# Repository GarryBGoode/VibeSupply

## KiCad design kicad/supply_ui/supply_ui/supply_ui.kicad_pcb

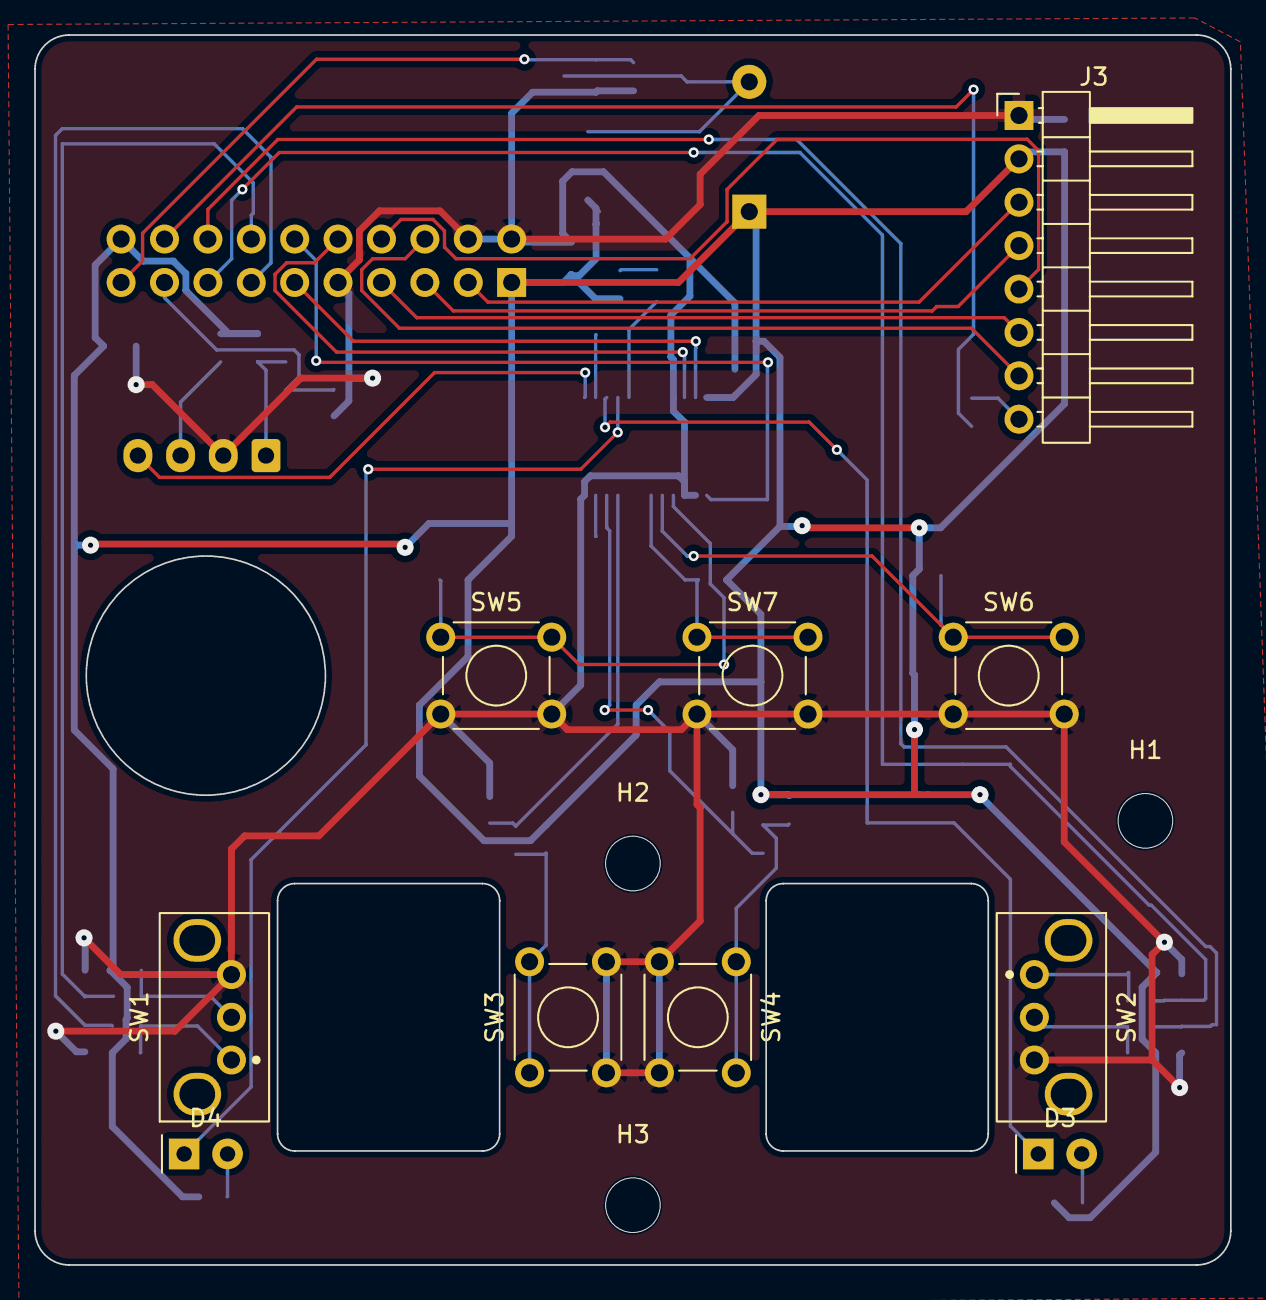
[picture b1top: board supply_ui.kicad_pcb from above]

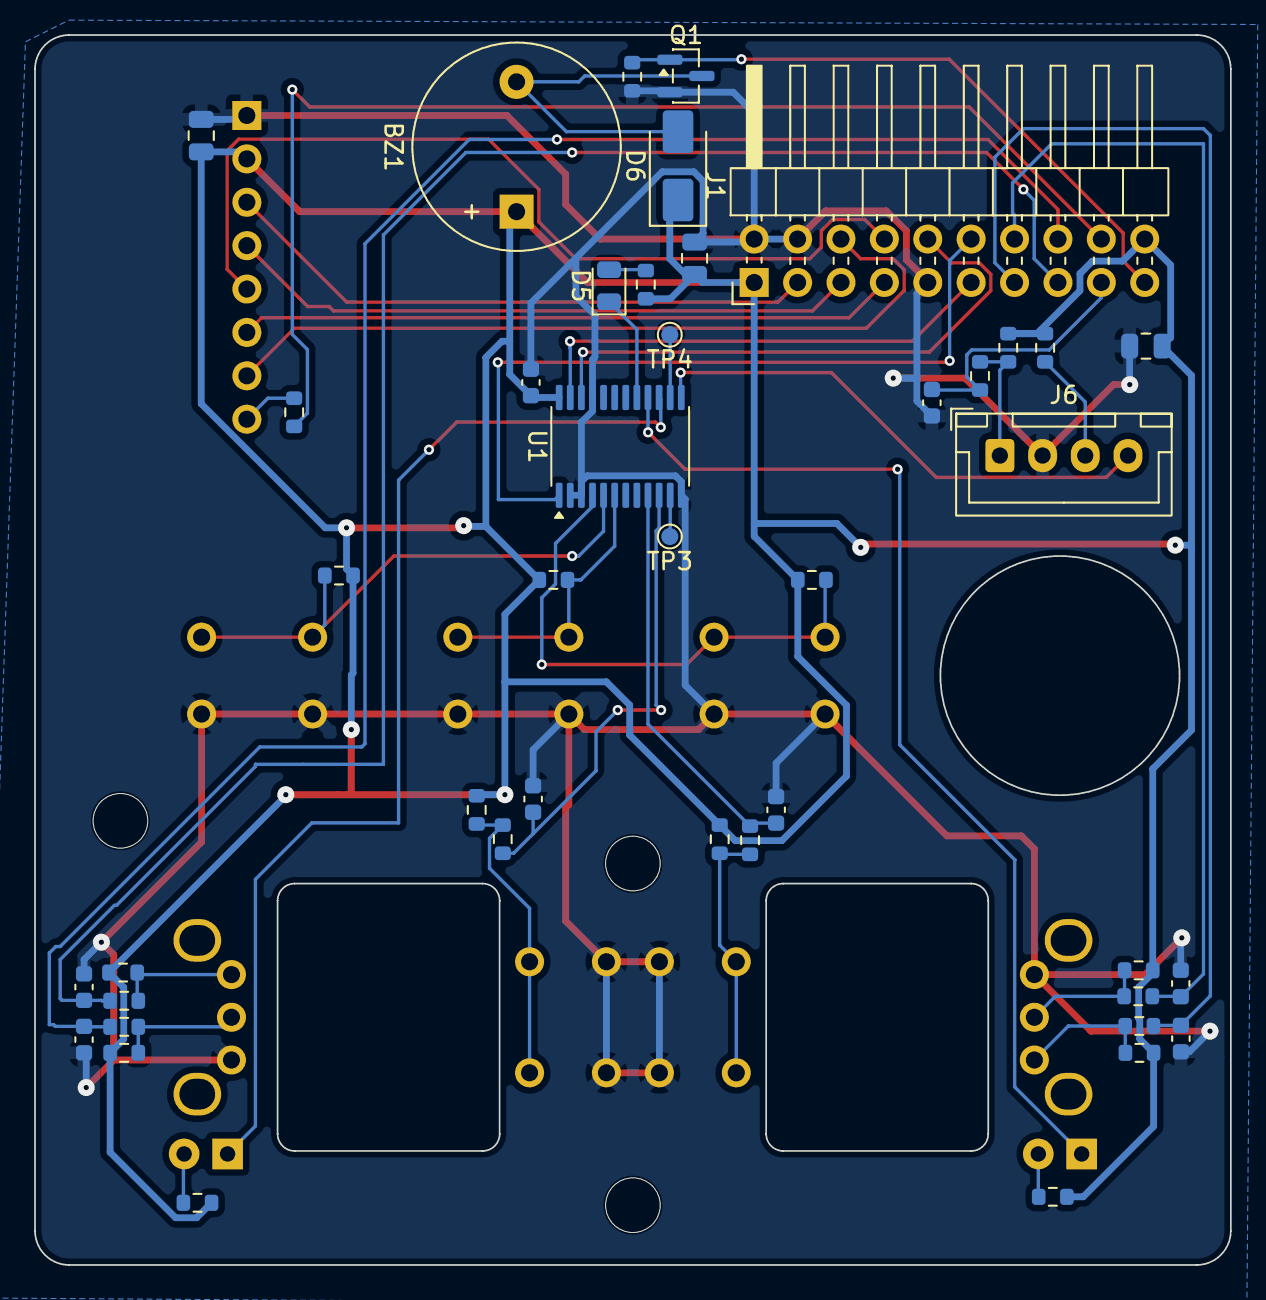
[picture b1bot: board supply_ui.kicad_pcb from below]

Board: 2 copper layers, 70.0 x 72.0 mm, 56 parts (43 on the bottom side), 41 nets.

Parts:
BZ1: magnetic 3V; Buzzer_12x9.5RM7.6
C1, C12: 10u; C_0805_2012Metric
C2: 100n; C_0805_2012Metric
C3, C4, C5, C6, C7, C8, C10: 10n; C_0603_1608Metric
C9: 100n; C_0603_1608Metric
D3: red 3mm diffused CC; LED_D3.0mm_Standoff
D4: green 3mm diffused CV; LED_D3.0mm_Standoff
D5: yellow; LED_0805_2012Metric
D6: SS14; D_SMA
H1, H2, H3: M3; MountingHole_3.2mm_M3
J1: to supply_control; PinHeader_2x10_P2.54mm_Horizontal
J3: IPS 1.9in ST7789 SPI (wired); PinHeader_1x08_P2.54mm_Horizontal
J6: OUTPUT panel button; JST_XH_B4B-XH-A_1x04_P2.50mm_Vertical
Q1: 2N7002; SOT-23
R1, R3, R5, R7, R9, R11, R15, R16, R17, R23: 10k; R_0603_1608Metric
R2, R4, R6, R8, R10, R12, R24: 1k; R_0603_1608Metric
R18, R19, R20: 330; R_0603_1608Metric
R27, R29: 100; R_0603_1608Metric
R28: 100k; R_0603_1608Metric
SW1, SW2: EC10E1220505; RotaryEncoder_Alps_EC10E_Horizontal
SW3: V WHEEL PUSH; SW_TH_Tactile_Omron_B3F-102x
SW4: I WHEEL PUSH; SW_TH_Tactile_Omron_B3F-102x
SW5: LEFT; SW_TH_Tactile_Omron_B3F-102x
SW6: RIGHT; SW_TH_Tactile_Omron_B3F-102x
SW7: ENTER; SW_TH_Tactile_Omron_B3F-102x
TP3, TP4: TestPoint; TestPoint_Pad_D1.0mm
U1: TCA9535PWR; TSSOP-24_4.4x7.8mm_P0.65mm

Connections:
+3V3: BZ1.1, C1.1, C2.1, C9.1, C12.1, D6.1, J1.1, J1.20, J3.2, R1.1, R3.1, R5.1, R7.1, R9.1, R11.1, R15.1, R16.1, R17.1, R18.1, R19.1, R20.1, R23.1, R27.1, U1.24
BTN_ENTER: R17.2, SW7.1, U1.6
BTN_LEFT: R15.2, SW5.1, U1.4
BTN_RIGHT: R16.2, SW6.1, U1.5
BUZZER: J1.19, Q1.1, R28.1
BUZZER_K: BZ1.2, D6.2, Q1.3
ENC1_A: C3.1, J1.13, R2.2
ENC1_A_RAW: R1.2, R2.1, SW1.A
ENC1_B: C4.1, J1.14, R4.2
ENC1_B_RAW: R3.2, R4.1, SW1.B
ENC1_SW: C5.1, R6.2, U1.9
ENC1_SW_RAW: R5.2, R6.1, SW3.1
ENC2_A: C6.1, J1.15, R8.2
ENC2_A_RAW: R7.2, R8.1, SW2.A
ENC2_B: C7.1, J1.16, R10.2
ENC2_B_RAW: R9.2, R10.1, SW2.B
ENC2_SW: C8.1, R12.2, U1.10
ENC2_SW_RAW: R11.2, R12.1, SW4.1
GND: C1.2, C2.2, C3.2, C4.2, C5.2, C6.2, C7.2, C8.2, C9.2, C10.2, C12.2, J1.2, J1.4, J1.9, J3.1, J6.2, Q1.2, R28.2, SW1.C, SW2.C, SW3.2, SW4.2, SW5.2, SW6.2, SW7.2, U1.2, U1.3, U1.12, U1.21
I2C2_SCL: J1.10, U1.22
I2C2_SDA: J1.11, U1.23
LCD_BL: J1.18, R29.1
LCD_BLK: J3.8, R29.2
LCD_CS: J1.6, J3.7
LCD_DC: J1.7, J3.6
LCD_MOSI: J1.5, J3.4
LCD_RST: J1.8, J3.5
LCD_SCK: J1.3, J3.3
LED_CC_K: D3.1, U1.15
LED_CV_K: D4.1, U1.16
LED_FAULT_K: D5.1, U1.17
LED_OE_K: J6.4, U1.13
unnamed: TP3.1, U1.11
unnamed: D3.2, R18.2
unnamed: D4.2, R19.2
unnamed: D5.2, R20.2
unnamed: TP4.1, U1.14
OE_BTN: C10.1, J1.17, R24.2
OE_BTN_RAW: J6.1, R23.2, R24.1
OE_LED_A: J6.3, R27.2
UI_INT: J1.12, U1.1

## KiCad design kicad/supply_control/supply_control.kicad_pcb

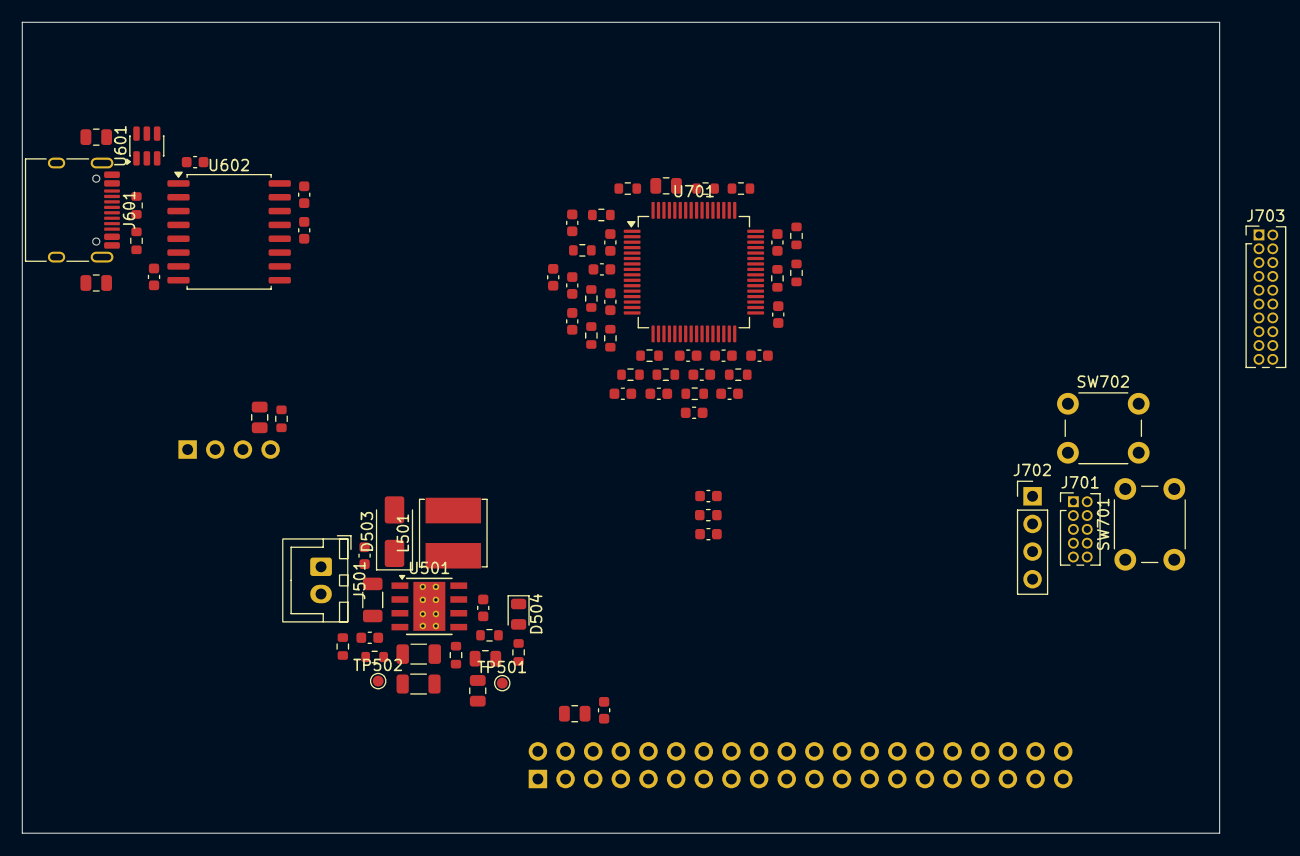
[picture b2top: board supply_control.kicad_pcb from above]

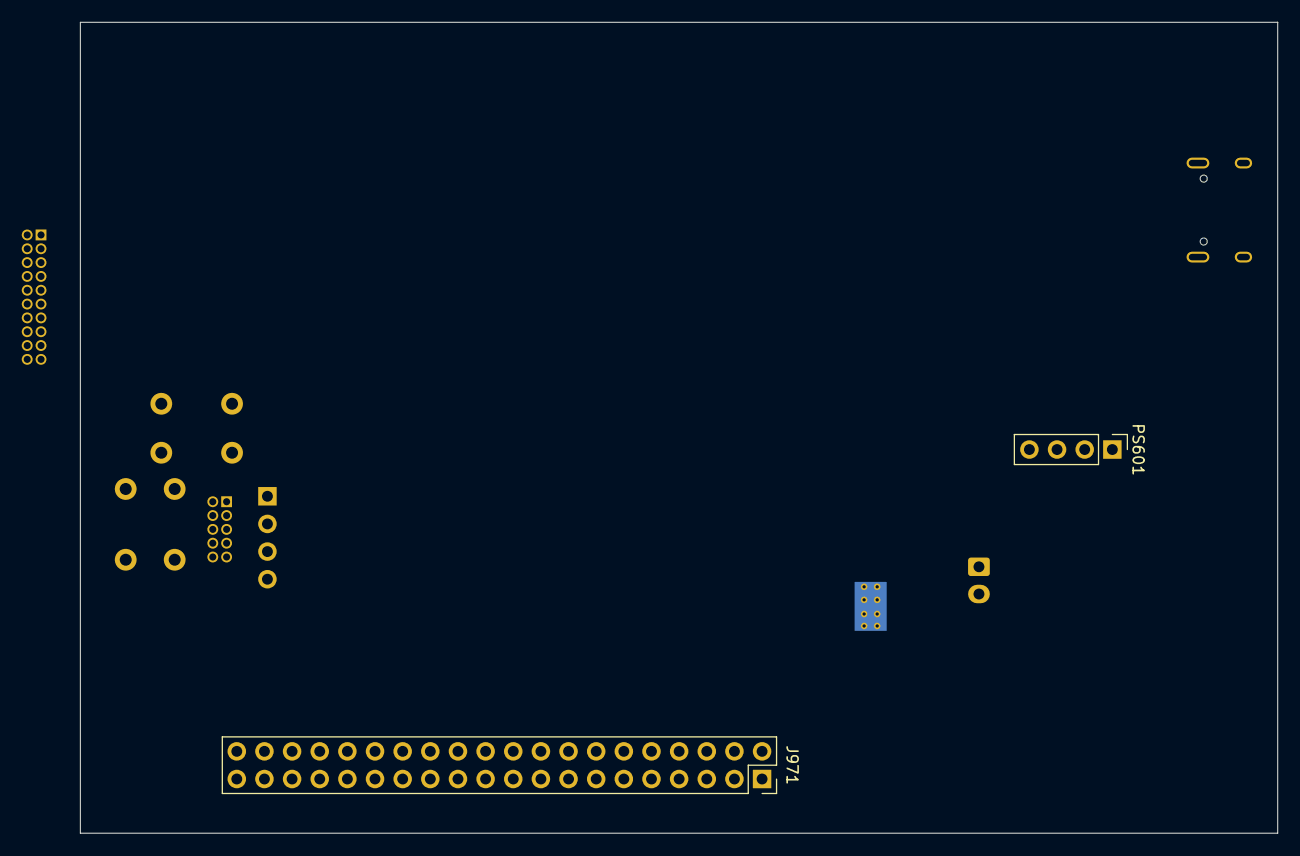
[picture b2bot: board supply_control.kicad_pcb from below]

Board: 4 copper layers, 110.0 x 74.5 mm, 80 parts (2 on the bottom side), 77 nets, no tracks yet.

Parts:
C501, C502: 2.2u; C_1206_3216Metric
C503, C504, C508, C604, C605, C701, C702, C703, C704, C706, C708, C709, C972: 100n; C_0603_1608Metric
C505, C506: 22u; C_0805_2012Metric
C507, C602, C603, C707: 1u; C_0603_1608Metric
C509: 10n; C_0603_1608Metric
C601, C606, C607, C705, C971: 4.7u; C_0805_2012Metric
C710, C711, C712, C713, C714, C715, C716, C717, C718: 1n; C_0603_1608Metric
D503: SS14; D_SMA
D504: green; LED_0805_2012Metric
FB501: 600R@100MHz; L_0603_1608Metric
J501: POWER rocker; JST_XH_B2B-XH-A_1x02_P2.50mm_Vertical
J601: USB_C_Receptacle_USB2.0_16P; USB_C_Receptacle_HRO_TYPE-C-31-M-12
J701: SWD; PinHeader_2x05_P1.27mm_Vertical
J702: UART; PinHeader_1x04_P2.54mm_Vertical
J703: UI ribbon; PinHeader_2x10_P1.27mm_Vertical
J971: B2B to supply_power; PinSocket_2x20_P2.54mm_Vertical
L501: 22uH; L_Bourns_SRN6045TA
PS601: B0505S-1WR3; PinHeader_1x04_P2.54mm_Vertical
R501: 66.5k; R_0603_1608Metric
R502: 23.2k; R_0603_1608Metric
R503, R701, R706, R707: 10k; R_0603_1608Metric
R504: 1k; R_0603_1608Metric
R505: 4.7k; R_1206_3216Metric
R506: 47k; R_0603_1608Metric
R601, R602: 5.1k; R_0603_1608Metric
R603, R704, R705: 2.2k; R_0603_1608Metric
R702, R703: 4.7k; R_0603_1608Metric
R708, R709, R710, R711, R712, R713, R714, R715, R716: 100; R_0603_1608Metric
SW701: RESET; SW_PUSH_6mm
SW702: BOOT; SW_PUSH_6mm
TP501, TP502: TestPoint; TestPoint_Pad_D1.0mm
U501: LMR38010; TI_SO-PowerPAD-8_ThermalVias
U601: USBLC6-2SC6; SOT-23-6
U602: ADUM3160; SOIC-16W_7.5x10.3mm_P1.27mm
U701: STM32G474RETx; LQFP-64_10x10mm_P0.5mm

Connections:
+3V3: C505.1, C506.1, C603.1, C605.1, C701.1, C702.1, C703.1, C704.1, C705.1, C971.1, C972.1, FB501.1, J701.1, J702.1, J703.1, J703.20, J971.5, J971.6, L501.2, R502.1, R504.1, R702.1, R703.1, R704.1, R705.1, R706.1, R707.1, SW702.2, TP501.1, U602.12, U602.13, U602.14, U602.16, U701.1, U701.16, U701.32, U701.48, U701.64
+3V3A: C507.1, C508.1, C706.1, FB501.2, U701.29
+5V_ISO: C607.1, D503.2, PS601.4, R603.1
BOOT0: R701.1, SW702.1, U701.61
BUCK_PSKIP: J971.15, U701.36
BUCK_RUN: J971.16, U701.34
BUZZER: J703.19, U701.21
CLAMP_DIS: J971.18, U701.59
DAC_I: J971.26, U701.19
DAC_ICL: J971.28, U701.20
DAC_V: J971.24, U701.18
DCIN_ON: J971.21, U701.57
ENC1_A: J703.13, U701.38
ENC1_B: J703.14, U701.39
ENC2_A: J703.15, U701.8
ENC2_B: J703.16, U701.9
FAULT: J971.17, U701.4
GND: C501.2, C502.2, C503.2, C505.2, C506.2, C507.2, C508.2, C509.2, C603.2, C605.2, C607.2, C701.2, C702.2, C703.2, C704.2, C705.2, C706.2, C707.2, C708.2, C709.2, C710.2, C711.2, C712.2, C713.2, C714.2, C715.2, C716.2, C717.2, C718.2, C971.2, C972.2, D504.1, J701.3, J701.5, J701.9, J702.4, J703.2, J703.4, J703.9, J971.1, J971.3, J971.4, J971.7, J971.8, J971.22, J971.23, J971.25, J971.27, J971.33, J971.39, J971.40, PS601.3, R501.2, R503.2, R506.2, R603.2, R701.2, SW701.2, U501.1, U501.9, U602.9, U602.15, U701.15, U701.27, U701.31, U701.47, U701.63
GND_ISO: C601.2, C602.2, C604.2, C606.2, J601.A1, J601.A12, J601.B1, J601.B12, J601.SH, PS601.1, R601.2, R602.2, U601.2, U602.2, U602.8
I2C1_SCL: J971.10, R702.2, U701.51
I2C1_SDA: J971.9, R703.2, U701.60
I2C2_SCL: J703.10, R704.2, U701.43
I2C2_SDA: J703.11, R705.2, U701.42
IL_SNS: J971.29, R711.1
IL_SNS_MCU: C713.1, R711.2, U701.24
INA_ALERT: J971.11, R707.2, U701.3
ISO_CC1: J601.A5, R601.1
ISO_CC2: J601.B5, R602.1
ISO_UD+: J601.A6, J601.B6, U601.1, U601.6, U602.7
ISO_UD-: J601.A7, J601.B7, U601.3, U601.4, U602.6
ISO_VDD1: C602.1, C604.1, U602.3, U602.4, U602.5
ITH_MON: J971.34, R713.1
ITH_MON_MCU: C715.1, R713.2, U701.10
LCD_BL: J703.18, U701.30
LCD_CS: J703.6, U701.40
LCD_DC: J703.7, U701.41
LCD_MOSI: J703.5, U701.37
LCD_RST: J703.8, U701.54
LCD_SCK: J703.3, U701.35
LOGIC_IN: C501.1, C502.1, C503.1, D503.1, J971.2, R505.1, U501.3
LOG_BOOT: C504.1, U501.7
LOG_EN: C509.1, J501.2, R506.1, TP502.1, U501.2
LOG_FB: R502.2, R503.1, U501.5
LOG_SW: C504.2, L501.1, U501.8
unnamed: J501.1, R505.2
unnamed: R501.1, U501.4
unnamed: D504.2, R504.2
unnamed: J701.2, U701.49
unnamed: J701.4, U701.50
NRST: C709.1, J701.10, SW701.1, U701.7
NTC_CLAMP: J971.38, R716.1
NTC_CLAMP_MCU: C718.1, R716.2, U701.23
NTC_FET: J971.36, R714.1
NTC_FET_MCU: C716.1, R714.2, U701.11
NTC_IND: J971.35, R715.1
NTC_IND_MCU: C717.1, R715.2, U701.22
NTC_OUTSW: J971.37, R712.1
NTC_OUTSW_MCU: C714.1, R712.2, U701.26
OCP_FLT: J971.19, U701.25
OE_BTN: J703.17, U701.55
OUT_EN: J971.13, U701.58
OVP_FLT: J971.20, U701.12
PD_IRQ: J971.12, U701.62
PD_SINK_EN: J971.14, U701.56
UART_RX: J702.3, U701.53
UART_TX: J702.2, U701.52
UI_INT: J703.12, R706.2, U701.44
USB_DM: U602.11, U701.45
USB_DP: U602.10, U701.46
VBUS_PC: C601.1, C606.1, J601.A4, J601.A9, J601.B4, J601.B9, PS601.2, U601.5, U602.1
VIN_SNS: J971.31, R710.1
VIN_SNS_MCU: C712.1, R710.2, U701.17
VOUT_SNS: J971.30, R708.1
VOUT_SNS_MCU: C710.1, R708.2, U701.13
VREF+: C707.1, C708.1, U701.28
VTERM_SNS: J971.32, R709.1
VTERM_SNS_MCU: C711.1, R709.2, U701.14

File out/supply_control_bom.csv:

Qty,Refs,Part,Value,Footprint,LCSC,DNP
2,C501 C502,C,2.2u,Capacitor_SMD:C_1206_3216Metric,,
13,C503 C504 C508 C604 C605 C701 C702 C703 C704 C706 C708 C709 C972,C,100n,Capacitor_SMD:C_0603_1608Metric,,
2,C505 C506,C,22u,Capacitor_SMD:C_0805_2012Metric,,
4,C507 C602 C603 C707,C,1u,Capacitor_SMD:C_0603_1608Metric,,
1,C509,C,10n,Capacitor_SMD:C_0603_1608Metric,,
5,C601 C606 C607 C705 C971,C,4.7u,Capacitor_SMD:C_0805_2012Metric,,
9,C710 C711 C712 C713 C714 C715 C716 C717 C718,C,1n,Capacitor_SMD:C_0603_1608Metric,,
1,D503,D_Schottky,SS14,Diode_SMD:D_SMA,,
1,D504,LED,green,LED_SMD:LED_0805_2012Metric,,
1,FB501,FerriteBead_Small,600R@100MHz,Inductor_SMD:L_0603_1608Metric,,
1,J501,Conn_01x02,POWER rocker,Connector_JST:JST_XH_B2B-XH-A_1x02_P2.50mm_Vertical,,
1,J601,USB_C_Receptacle_USB2.0_16P,USB_C_Receptacle_USB2.0_16P,Connector_USB:USB_C_Receptacle_HRO_TYPE-C-31-M-12,C2765186,
1,J701,Conn_02x05_Odd_Even,SWD,Connector_PinHeader_1.27mm:PinHeader_2x05_P1.27mm_Vertical,,
1,J702,Conn_01x04,UART,Connector_PinHeader_2.54mm:PinHeader_1x04_P2.54mm_Vertical,,
1,J703,Conn_02x10_Odd_Even,UI ribbon,Connector_PinHeader_2.54mm:PinHeader_2x10_P2.54mm_Horizontal,,
1,J971,Conn_02x20_Odd_Even,B2B to supply_power,Connector_PinSocket_2.54mm:PinSocket_2x20_P2.54mm_Vertical,,
1,L501,L,22uH,Inductor_SMD:L_Bourns_SRN6045TA,,
1,PS601,B0505S-1WR3,B0505S-1WR3,Connector_PinHeader_2.54mm:PinHeader_1x04_P2.54mm_Vertical,C7465178,
1,R501,R,66.5k,Resistor_SMD:R_0603_1608Metric,,
1,R502,R,23.2k,Resistor_SMD:R_0603_1608Metric,,
4,R503 R701 R706 R707,R,10k,Resistor_SMD:R_0603_1608Metric,,
1,R504,R,1k,Resistor_SMD:R_0603_1608Metric,,
1,R505,R,4.7k,Resistor_SMD:R_1206_3216Metric,,
1,R506,R,47k,Resistor_SMD:R_0603_1608Metric,,
2,R601 R602,R,5.1k,Resistor_SMD:R_0603_1608Metric,,
3,R603 R704 R705,R,2.2k,Resistor_SMD:R_0603_1608Metric,,
2,R702 R703,R,4.7k,Resistor_SMD:R_0603_1608Metric,,
9,R708 R709 R710 R711 R712 R713 R714 R715 R716,R,100,Resistor_SMD:R_0603_1608Metric,,
1,SW701,SW_Push,RESET,Button_Switch_THT:SW_PUSH_6mm,,
1,SW702,SW_Push,BOOT,Button_Switch_THT:SW_PUSH_6mm,,
2,TP501 TP502,TestPoint,TestPoint,TestPoint:TestPoint_Pad_D1.0mm,,
1,U501,LMR38010,LMR38010,Package_SO:TI_SO-PowerPAD-8_ThermalVias,C5219310,
1,U601,USBLC6-2SC6,USBLC6-2SC6,Package_TO_SOT_SMD:SOT-23-6,,
1,U602,ADUM3160,ADUM3160,Package_SO:SOIC-16W_7.5x10.3mm_P1.27mm,C284149,
1,U701,STM32G474RETx,STM32G474RETx,Package_QFP:LQFP-64_10x10mm_P0.5mm,C521608,

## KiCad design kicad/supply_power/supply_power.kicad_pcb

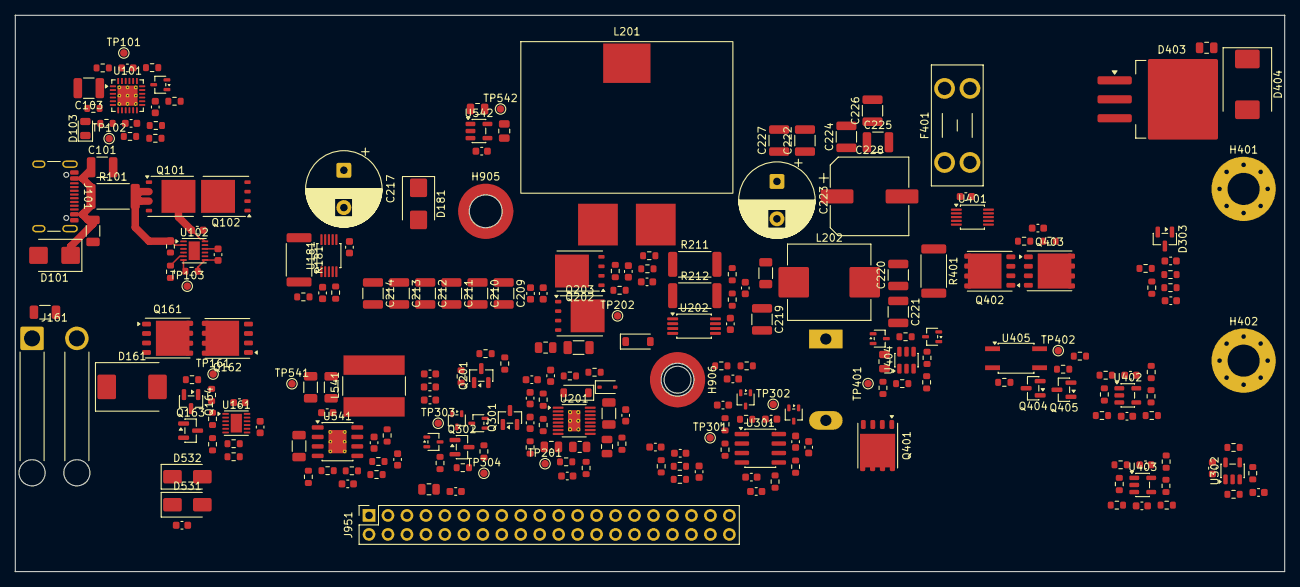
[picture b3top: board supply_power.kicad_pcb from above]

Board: 4 copper layers, 170.0 x 74.5 mm, 253 parts (1 on the bottom side), 125 nets.

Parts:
C101, C103, C209, C210, C211, C212, C213, C214, C219, C220, C221, C222, C224, C225, C226, C227: 4.7u; C_1210_3225Metric
C102, C161, C201: 1u; C_1206_3216Metric
C104, C305, C532: 1u; C_0603_1608Metric
C105, C106, C107, C108, C162, C163, C181, C182, C207, C215, C216, C229, C231, C232, C301, C302, C304, C313, C314, C401, C403, C405, C408, C409, C531, C533, C542, C952: 100n; C_0603_1608Metric
C202, C406, C549: 1u; C_0805_2012Metric
C203, C951: 4.7u; C_0805_2012Metric
C204, C218, C230, C310, C402, C404, C545: 1n; C_0603_1608Metric
C205: 100p; C_0603_1608Metric
C206, C303, C311, C312, C548: 10n; C_0603_1608Metric
C208: 1n; C_0805_2012Metric
C217: 100u 100V; CP_Radial_D10.0mm_P5.00mm
C223: 100u 63V; CP_Radial_D10.0mm_P5.00mm
C228: 100u 63V; CP_Elec_10x12.6
C306, C309: 1.3n; C_0603_1608Metric
C307: 68p; C_0603_1608Metric
C308: 27n; C_0603_1608Metric
C407: 100n; C_0805_2012Metric
C541: 2.2u; C_1206_3216Metric
C543: 2.2n; C_0603_1608Metric
C544: 3.3n; C_0603_1608Metric
C546, C547: 10u; C_1206_3216Metric
C550: 2.2u; C_0805_2012Metric
D101: SMBJ30A; D_SMB
D102, D301, D302, D304, D305, D306, D401, D402: BAT54W; SOT-323_SC-70
D103: green; LED_0805_2012Metric
D161, D404: SMCJ54A; D_SMC
D162: BZT52C12; D_SOD-123
D181: SMBJ33A; D_SMB
D201: BZT52C36; D_SOD-123
D202: CMDSH-4E; D_SOD-323
D303: BAT54S; SOT-23
D403: MBRB40100CT; TO-263-3_TabPin2
D531, D532: SS110; D_SMA
F401: 15A 32V MINI; Fuseholder_Blade_Mini_Keystone_3568
FB531: 600R@100MHz; L_0603_1608Metric
H401: POST+; MountingHole_4.3mm_M4_Pad_Via
H402: POST-; MountingHole_4.3mm_M4_Pad_Via
H905: GND screw (M3 insert); Mounting_Wuerth_WA-SMSI-M3_H3mm_9774030360
H906: LTO100 screw (M3 insert); Mounting_Wuerth_WA-SMSI-M3_H3mm_9774030360
J101: USB_C_Receptacle_USB2.0_16P; USB_C_Receptacle_GCT_USB4105-xx-A_16P_TopMnt_Horizontal
J161: DC IN wires; SolderWire-1.5sqmm_1x02_P6mm_D1.7mm_OD3mm_Relief
J951: B2B to supply_control; PinSocket_2x20_P2.54mm_Vertical
L201: 10uH SER2918H-103KL; L_Coilcraft_SER2918H
L202: 0.47uH; L_Changjiang_FXL1040
L541: 68uH; L_Bourns-SRN8040_8x8.15mm
Q101, Q102: CSD18540Q5B; TDSON-8-1
Q161, Q162: ISC030N10NM6; Infineon_PG-TDSON-8_6.15x5.15mm
Q163, Q164, Q201, Q302, Q404, Q405: 2N7002; SOT-23
Q202, Q203: CSD18531Q5A; TDSON-8-1
Q301: BC857; SOT-23
Q401, Q402, Q403: BSC040N10NS5; Infineon_PG-TDSON-8_6.15x5.15mm
R101: 5m; R_2512_6332Metric
R102: 200; R_0603_1608Metric
R103, R104: 5.1k; R_0603_1608Metric
R105, R108, R109, R163, R166, R207, R309, R317, R319, R414, R415, R418, R422, R541, R543: 100k; R_0603_1608Metric
R106, R107, R205, R206, R301, R302: 1k; R_0603_1608Metric
R110, R161: 243k; R_0603_1608Metric
R111, R162, R183, R203, R217, R218, R219, R305, R307, R311, R313, R314, R316, R318, R403, R404, R409, R410, R421, R423, R424, R545: 10k; R_0603_1608Metric
R164: 15k; R_0603_1608Metric
R165, R407, R413: 1M; R_0603_1608Metric
R181, R401: 1m; R_2512_6332Metric
R182, R408: 120k; R_0603_1608Metric
R201: 10; R_0805_2012Metric
R202: 61.9k; R_0603_1608Metric
R204: 124k; R_0603_1608Metric
R208: 1; R_0603_1608Metric
R209: 0; R_0603_1608Metric
R210: 2.2; R_1206_3216Metric
R211, R212: 4m; R_2512_6332Metric
R213, R214: 10; R_0603_1608Metric
R215: 0.1; R_1206_3216Metric
R216, R406, R412: 4.7k; R_0603_1608Metric
R303: 100; R_0603_1608Metric
R304, R402: 91.9k; R_0603_1608Metric
R306: 47.5k; R_0603_1608Metric
R308: 2.4k; R_0603_1608Metric
R310, R312: 110k; R_0603_1608Metric
R315: 11.5k; R_0603_1608Metric
R405, R546: 470k; R_0603_1608Metric
R411: 10.2k; R_0603_1608Metric
R416: 4.7; R_0603_1608Metric
R417: 2.2; R_0603_1608Metric
R419: 2R 100W LTO100; TO-247-2_Horizontal_TabDown
R420: 91; R_0603_1608Metric
R542: 22k; R_0603_1608Metric
R544: 90.9k; R_0603_1608Metric
TH101, TH201, TH202, TH401, TH402: 10k B3950; R_0603_1608Metric
TP101, TP102, TP103, TP161, TP201, TP202, TP301, TP302, TP303, TP304, TP401, TP402, TP541, TP542: TestPoint; TestPoint_Pad_D1.0mm
U101: AP33772S; QFN-24-1EP_4x4mm_P0.5mm_EP2.7x2.7mm_ThermalVias
U102, U161: LM74800; WSON-12-1EP_3x3mm_P0.5mm_EP1.5x2.5mm
U181, U401: INA228; TSSOP-10_3x3mm_P0.5mm
U201: LTC7803; MSOP-16-1EP_3x4.039mm_P0.5mm_EP1.651x2.845mm_ThermalVias
U202: INA240A3PW; TSSOP-8_4.4x3mm_P0.65mm
U301: ADA4522-2; SOIC-8_3.9x4.9mm_P1.27mm
U302, U402, U403: LMV331; SOT-23-5
U404: UCC27511ADBV; SOT-23-6
U405: VOM1271; SO-4_4.4x3.6mm_P2.54mm
U541: LM5164DDA; HSOP-8-1EP_3.9x4.9mm_P1.27mm_EP2.41x3.1mm_ThermalVias
U542: LP2985-5.0; SOT-23-5

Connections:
+3V3: C181.1, C401.1, C951.1, C952.1, FB531.1, J951.5, J951.6, R207.1, R316.1, R420.1, U181.6, U401.2, U401.6
+3V3A: C532.1, C533.1, D303.2, FB531.2, R218.1, R219.1, R423.1, R424.1
+5VA: C229.1, C304.1, C305.1, C314.1, C403.1, C405.1, C550.1, D102.1, R314.1, R405.1, R406.1, R410.1, R412.1, TP542.1, U202.5, U301.8, U302.5, U402.5, U403.5, U542.5
+12V_AUX: C202.1, C406.1, C544.2, C546.1, C547.1, C549.1, L541.2, R544.1, TP541.1, U201.11, U404.1, U542.1, U542.3
AUX_BST: C543.1, U541.7
AUX_EN: R541.2, R542.1, U541.3
AUX_FB: C545.2, R544.2, R545.1, U541.5
AUX_RA: C544.1, C545.1, R546.2
AUX_SW: C543.2, L541.1, R546.1, U541.8
BUCK_BG: R209.1, U201.13
BUCK_BOOST: C207.1, D202.1, U201.14
BUCK_INTVCC: C203.1, D202.2, R202.1, R205.1, U201.10
BUCK_MODE: R205.2, R206.1, U201.9
BUCK_MODE_LO: Q201.3, R206.2
BUCK_PSKIP: J951.16, Q201.1, R207.2
BUCK_RUN: J951.15, R318.1
BUCK_SENSE_N: C218.2, R214.2, U201.3
BUCK_SENSE_P: C218.1, R213.2, U201.2
BUCK_SS: C206.1, U201.1
BUCK_TG: R208.1, U201.15
BUCK_VFB: C204.1, R202.2, R203.1, U201.4
BUCK_VINC: C201.1, D201.1, R201.2, U201.12
CC_M: C309.1, R307.2, R308.1, U301.6
CC_OUT: D302.3, TP302.1, U301.7
CC_Z: C308.1, R308.2
CLAMP_BUS_CMP: D402.1, R412.2, R413.1, U403.4
CLAMP_BUS_REF: R410.2, R411.1, U403.3
CLAMP_BUS_SNS: C404.1, R408.2, R409.1, R413.2, U403.1
CLAMP_CMP: D401.1, R406.2, R407.1, U402.4
CLAMP_DIS: J951.17, R415.1, U404.5
CLAMP_G: Q401.4, R416.2, R417.2, R418.1, TP401.1
CLAMP_IN: D401.3, D402.3, R414.1, U404.6
CLAMP_R: Q401.5, R419.2
CLAMP_REF: R404.2, R405.2, U402.3
CLAMP_SNS: C402.1, R402.2, R403.1, R407.2, U402.1
CV_M: C307.1, R304.2, R305.1, R306.1, U301.2
CV_OUT: D301.3, TP301.1, U301.1
CV_Z: C306.1, R306.2
DACICL_F: C303.1, Q301.1, R303.2
DACI_F: C302.1, R302.2, U301.5
DACV_F: C301.1, R301.2, R404.1, U301.3
DAC_I: J951.25, R302.1
DAC_ICL: J951.27, R303.1
DAC_V: J951.23, R301.1
DCIN_EN: Q163.3, R163.2, R164.1, U161.6
DCIN_HOLD: D162.1, Q163.1, Q164.3, R165.2
DCIN_MID: C162.1, C163.2, Q161.5, Q162.5, R163.1, U161.3, U161.10, U161.12
DCIN_ON: J951.22, Q164.1, R166.1, TP161.1
DCIN_RAW: C161.1, D161.1, D532.2, J161.1, Q161.1, Q161.2, Q161.3, U161.2
FAULT: D304.3, D305.3, D306.3, J951.18, Q302.1, Q405.1, R317.1, TP303.1
GND: C101.2, C102.2, C103.2, C104.2, C105.2, C106.2, C107.2, C161.2, C162.2, C181.2, C182.2, C201.2, C202.2, C203.2, C204.2, C205.2, C206.2, C208.2, C209.2, C210.2, C211.2, C212.2, C213.2, C214.2, C215.2, C216.2, C217.2, C219.2, C220.2, C221.2, C222.2, C223.2, C224.2, C225.2, C226.2, C227.2, C228.2, C229.2, C230.2, C231.2, C232.2, C301.2, C302.2, C303.2, C304.2, C305.2, C310.2, C311.2, C312.2, C313.2, C314.2, C401.2, C402.2, C403.2, C404.2, C405.2, C406.2, C407.2, C408.2, C409.2, C531.2, C532.2, C533.2, C541.2, C542.2, C546.2, C547.2, C548.2, C549.2, C550.2, C951.2, C952.2, D101.2, D103.1, D161.2, D162.2, D181.2, D201.2, D303.1, D403.1, D403.3, D404.2, H402.1, H905.1, H906.1, J101.A1, J101.A12, J101.B1, J101.B12, J101.SH, J161.2, J951.2, J951.3, J951.4, J951.7, J951.8, J951.21, J951.24, J951.26, J951.28, J951.34, J951.39, J951.40, Q163.2, Q164.2, Q201.2, Q203.1, Q203.2, Q203.3, Q301.3, Q302.2, Q401.1, Q401.2, Q401.3, Q404.2, Q405.2, R103.2, R104.2, R105.2, R108.2, R109.2, R111.2, R162.2, R164.2, R166.2, R183.2, R203.2, R204.2, R217.2, R305.2, R311.2, R313.2, R315.2, R317.2, R319.2, R403.2, R409.2, R411.2, R414.2, R415.2, R418.2, R422.2, R542.2, R543.2, R545.2, TH101.2, TH201.2, TH202.2, TH401.2, TH402.2, U101.3, U101.25, U102.7, U161.7, U181.1, U181.2, U181.7, U201.8, U201.17, U202.1, U202.4, U202.6, U202.7, U301.4, U302.2, U401.1, U401.7, U402.2, U403.2, U404.4, U541.1, U541.9, U542.2
HW_OVP: D306.1, R316.2, U302.4
HW_OVP_REF: C313.1, R314.2, R315.1, U302.3
I2C1_SCL: J951.9, U101.5, U181.5, U401.5
I2C1_SDA: J951.10, U101.4, U181.4, U401.4
IL_AMP: R216.1, R307.1, U202.8
IL_SENSE+: L201.2, R211.1, R212.1, R213.1, U202.2
IL_SNS: C230.1, J951.30, R216.2, R217.1
INA_ALERT: J951.12, U181.3, U401.3
ITH: C205.1, C306.2, C307.2, C308.2, C309.2, D301.1, D302.1, Q301.2, R309.1, TP201.1, U201.5
ITH_MON: C310.1, J951.33, R309.2
LOGIC_IN: C531.1, D531.1, D532.1, J951.1, R165.1
unnamed: R102.2, U101.22
unnamed: TP101.1, U101.23
unnamed: C105.1, U101.12
unnamed: C106.1, U101.15
unnamed: TH101.1, U101.13
unnamed: R105.1, U101.11
unnamed: R106.1, U101.8
unnamed: D103.2, R106.2
unnamed: TP102.1, U101.6
unnamed: R107.1, U101.9
unnamed: Q101.4, U102.1
unnamed: Q102.4, U102.8
unnamed: C108.1, U102.11
unnamed: R110.1, U102.4
unnamed: R110.2, R111.1, U102.5
unnamed: Q161.4, U161.1
unnamed: Q162.4, U161.8
unnamed: C163.1, U161.11
unnamed: R161.1, U161.4
unnamed: R161.2, R162.1, U161.5
unnamed: R204.1, U201.7
unnamed: Q202.4, R208.2
unnamed: Q203.4, R209.2
unnamed: C208.1, R210.2
unnamed: R416.1, U404.2
unnamed: R417.1, U404.3
unnamed: R543.1, U541.4
unnamed: C548.1, U542.4
NTC_CLAMP: C408.1, J951.37, R423.2, TH401.1
NTC_FET: C231.1, J951.35, R218.2, TH201.1
NTC_IND: C232.1, J951.36, R219.2, TH202.1
NTC_OUTSW: C409.1, J951.38, R424.2, TH402.1
OCP_FLT: D305.1, J951.20
OE_G: Q404.1, Q405.3, R421.2, R422.1
OE_LED_A: R420.2, U405.1
OE_LED_K: Q404.3, U405.2
OUT+: C407.1, D403.2, D404.1, F401.2, H401.1, R312.1
OUTSW_G: Q402.4, Q403.4, TP402.1, U405.4
OUTSW_MID: Q402.1, Q402.2, Q402.3, Q403.1, Q403.2, Q403.3, U405.3
OUT_EN: J951.14, R421.1
OVP_FLT: D304.1, J951.19
PD_CC1: J101.A5, R103.1, U101.17
PD_CC2: J101.B5, R104.1, U101.16
PD_DN: J101.A7, J101.B7, U101.18
PD_DP: J101.A6, J101.B6, U101.19
PD_IRQ: J951.11, R107.2, R108.1
PD_SINK_EN: J951.13, R109.1, TP103.1, U102.6
PD_V5V: C104.1, D102.3, U101.20
RUN: Q302.3, R318.2, R319.1, TP304.1, U201.6
SW: C207.2, L201.1, Q202.1, Q202.2, Q202.3, Q203.5, R210.1, TP202.1, U201.16
USBIN_MID: C107.1, C108.2, Q101.5, Q102.5, U102.3, U102.10, U102.12
VBUS_RAW: C101.1, C102.1, D101.1, D531.2, J101.A4, J101.A9, J101.B4, J101.B9, R101.1, U101.24
VBUS_S: C103.1, Q101.1, Q101.2, Q101.3, R101.2, R102.1, U101.1, U102.2
VC1: C219.1, C220.1, C221.1, C222.1, L202.1, R211.2, R212.2, R214.1, R215.1, U202.3
VC1_DAMP: C223.1, R215.2
VIN_BUS: Q102.1, Q102.2, Q102.3, Q162.1, Q162.2, Q162.3, R181.1, U102.9, U161.9, U181.10
VIN_PWR: C209.1, C210.1, C211.1, C212.1, C213.1, C214.1, C215.1, C216.1, C217.1, C541.1, C542.1, D181.1, Q202.5, R181.2, R182.1, R201.1, R408.1, R541.1, U181.8, U181.9, U541.2
VIN_SNS: C182.1, J951.32, R182.2, R183.1
VOUT_INT: C224.1, C225.1, C226.1, C227.1, C228.1, L202.2, R304.1, R310.1, R401.1, U401.10
VOUT_SH: Q402.5, R401.2, R402.1, R419.1, U401.8, U401.9
VOUT_SNS: C311.1, J951.29, R310.2, R311.1, U302.1
VTERM: F401.1, Q403.5
VTERM_SNS: C312.1, D303.3, J951.31, R312.2, R313.1

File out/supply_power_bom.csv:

Qty,Refs,Part,Value,Footprint,LCSC,DNP
16,C101 C103 C209 C210 C211 C212 C213 C214 C219 C220 C221 C222 C224 C225 C226 C227,C,4.7u,Capacitor_SMD:C_1210_3225Metric,C913445,
3,C102 C161 C201,C,1u,Capacitor_SMD:C_1206_3216Metric,,
3,C104 C305 C532,C,1u,Capacitor_SMD:C_0603_1608Metric,,
28,C105 C106 C107 C108 C162 C163 C181 C182 C207 C215 C216 C229 C231 C232 C301 C302 C304 C313 C314 C401 C403 C405 C408 C409 C531 C533 C542 C952,C,100n,Capacitor_SMD:C_0603_1608Metric,,
3,C202 C406 C549,C,1u,Capacitor_SMD:C_0805_2012Metric,,
2,C203 C951,C,4.7u,Capacitor_SMD:C_0805_2012Metric,,
7,C204 C218 C230 C310 C402 C404 C545,C,1n,Capacitor_SMD:C_0603_1608Metric,,
1,C205,C,100p,Capacitor_SMD:C_0603_1608Metric,,
5,C206 C303 C311 C312 C548,C,10n,Capacitor_SMD:C_0603_1608Metric,,
1,C208,C,1n,Capacitor_SMD:C_0805_2012Metric,,
1,C217,C_Polarized,100u 100V,Capacitor_THT:CP_Radial_D10.0mm_P5.00mm,C443138,
1,C223,C_Polarized,100u 63V,Capacitor_THT:CP_Radial_D10.0mm_P5.00mm,C2691842,
1,C228,C_Polarized,100u 63V,Capacitor_SMD:CP_Elec_10x12.6,C5154285,
2,C306 C309,C,1.3n,Capacitor_SMD:C_0603_1608Metric,,
1,C307,C,68p,Capacitor_SMD:C_0603_1608Metric,,
1,C308,C,27n,Capacitor_SMD:C_0603_1608Metric,,
1,C407,C,100n,Capacitor_SMD:C_0805_2012Metric,,
1,C541,C,2.2u,Capacitor_SMD:C_1206_3216Metric,,
1,C543,C,2.2n,Capacitor_SMD:C_0603_1608Metric,,
1,C544,C,3.3n,Capacitor_SMD:C_0603_1608Metric,,
2,C546 C547,C,10u,Capacitor_SMD:C_1206_3216Metric,,
1,C550,C,2.2u,Capacitor_SMD:C_0805_2012Metric,,
1,D101,D_Zener,SMBJ30A,Diode_SMD:D_SMB,C113998,
8,D102 D301 D302 D304 D305 D306 D401 D402,BAT54W,BAT54W,Package_TO_SOT_SMD:SOT-323_SC-70,,
1,D103,LED,green,LED_SMD:LED_0805_2012Metric,,
2,D161 D404,D_Zener,SMCJ54A,Diode_SMD:D_SMC,C438116,
1,D162,D_Zener,BZT52C12,Diode_SMD:D_SOD-123,,
1,D181,D_Zener,SMBJ33A,Diode_SMD:D_SMB,C173526,
1,D201,D_Zener,BZT52C36,Diode_SMD:D_SOD-123,C19077420,
1,D202,D_Schottky,CMDSH-4E,Diode_SMD:D_SOD-323,C5240486,
1,D303,BAT54S,BAT54S,Package_TO_SOT_SMD:SOT-23,,
1,D403,D_Schottky_Dual_CommonCathode_AKA,MBRB40100CT,Package_TO_SOT_SMD:TO-263-3_TabPin2,,
2,D531 D532,D_Schottky,SS110,Diode_SMD:D_SMA,,
1,F401,Fuse,15A 32V MINI,Fuse:Fuseholder_Blade_Mini_Keystone_3568,,
1,FB531,FerriteBead_Small,600R@100MHz,Inductor_SMD:L_0603_1608Metric,,
1,H401,MountingHole_Pad,POST+,MountingHole:MountingHole_4.3mm_M4_Pad_Via,,
1,H402,MountingHole_Pad,POST-,MountingHole:MountingHole_4.3mm_M4_Pad_Via,,
1,H905,MountingHole_Pad,GND screw (M3 insert),Mounting_Wuerth:Mounting_Wuerth_WA-SMSI-M3_H3mm_9774030360,,
1,H906,MountingHole_Pad,LTO100 screw (M3 insert),Mounting_Wuerth:Mounting_Wuerth_WA-SMSI-M3_H3mm_9774030360,,
1,J101,USB_C_Receptacle_USB2.0_16P,USB_C_Receptacle_USB2.0_16P,Connector_USB:USB_C_Receptacle_GCT_USB4105-xx-A_16P_TopMnt_Horizontal,C3020560,
1,J161,Conn_01x02,DC IN wires,Connector_Wire:SolderWire-1.5sqmm_1x02_P6mm_D1.7mm_OD3mm_Relief,,
1,J951,Conn_02x20_Odd_Even,B2B to supply_control,Connector_PinSocket_2.54mm:PinSocket_2x20_P2.54mm_Vertical,,
1,L201,L,10uH SER2918H-103KL,supply1:L_Coilcraft_SER2918H,C3911665,
1,L202,L,0.47uH,Inductor_SMD:L_Changjiang_FXL1040,C475921,
1,L541,L,68uH,Inductor_SMD:L_Bourns-SRN8040_8x8.15mm,,
2,Q101 Q102,CSD18532Q5B,CSD18540Q5B,Package_TO_SOT_SMD:TDSON-8-1,C86513,
2,Q161 Q162,BSC040N10NS5,ISC030N10NM6,Package_SON:Infineon_PG-TDSON-8_6.15x5.15mm,C3278643,
6,Q163 Q164 Q201 Q302 Q404 Q405,2N7002,2N7002,Package_TO_SOT_SMD:SOT-23,,
2,Q202 Q203,CSD18531Q5A,CSD18531Q5A,Package_TO_SOT_SMD:TDSON-8-1,C2876524,
1,Q301,BC857,BC857,Package_TO_SOT_SMD:SOT-23,C556165,
3,Q401 Q402 Q403,BSC040N10NS5,BSC040N10NS5,Package_SON:Infineon_PG-TDSON-8_6.15x5.15mm,C534334,
1,R101,R,5m,Resistor_SMD:R_2512_6332Metric,C2903482,
1,R102,R,200,Resistor_SMD:R_0603_1608Metric,,
2,R103 R104,R,5.1k,Resistor_SMD:R_0603_1608Metric,,
15,R105 R108 R109 R163 R166 R207 R309 R317 R319 R414 R415 R418 R422 R541 R543,R,100k,Resistor_SMD:R_0603_1608Metric,,
6,R106 R107 R205 R206 R301 R302,R,1k,Resistor_SMD:R_0603_1608Metric,,
2,R110 R161,R,243k,Resistor_SMD:R_0603_1608Metric,,
22,R111 R162 R183 R203 R217 R218 R219 R305 R307 R311 R313 R314 R316 R318 R403 R404 R409 R410 R421 R423 R424 R545,R,10k,Resistor_SMD:R_0603_1608Metric,,
1,R164,R,15k,Resistor_SMD:R_0603_1608Metric,,
3,R165 R407 R413,R,1M,Resistor_SMD:R_0603_1608Metric,,
2,R181 R401,R,1m,Resistor_SMD:R_2512_6332Metric,C2903470,
2,R182 R408,R,120k,Resistor_SMD:R_0603_1608Metric,,
1,R201,R,10,Resistor_SMD:R_0805_2012Metric,,
1,R202,R,61.9k,Resistor_SMD:R_0603_1608Metric,,
1,R204,R,124k,Resistor_SMD:R_0603_1608Metric,,
1,R208,R,1,Resistor_SMD:R_0603_1608Metric,,
1,R209,R,0,Resistor_SMD:R_0603_1608Metric,,
1,R210,R,2.2,Resistor_SMD:R_1206_3216Metric,,
2,R211 R212,R,4m,Resistor_SMD:R_2512_6332Metric,C2904236,
2,R213 R214,R,10,Resistor_SMD:R_0603_1608Metric,,
1,R215,R,0.1,Resistor_SMD:R_1206_3216Metric,,
3,R216 R406 R412,R,4.7k,Resistor_SMD:R_0603_1608Metric,,
1,R303,R,100,Resistor_SMD:R_0603_1608Metric,,
2,R304 R402,R,91.9k,Resistor_SMD:R_0603_1608Metric,,
1,R306,R,47.5k,Resistor_SMD:R_0603_1608Metric,,
1,R308,R,2.4k,Resistor_SMD:R_0603_1608Metric,,
2,R310 R312,R,110k,Resistor_SMD:R_0603_1608Metric,,
1,R315,R,11.5k,Resistor_SMD:R_0603_1608Metric,,
2,R405 R546,R,470k,Resistor_SMD:R_0603_1608Metric,,
1,R411,R,10.2k,Resistor_SMD:R_0603_1608Metric,,
1,R416,R,4.7,Resistor_SMD:R_0603_1608Metric,,
1,R417,R,2.2,Resistor_SMD:R_0603_1608Metric,,
1,R419,R,2R 100W LTO100,Package_TO_SOT_THT:TO-247-2_Horizontal_TabDown,C3546229,
1,R420,R,91,Resistor_SMD:R_0603_1608Metric,,
1,R542,R,22k,Resistor_SMD:R_0603_1608Metric,,
1,R544,R,90.9k,Resistor_SMD:R_0603_1608Metric,,
5,TH101 TH201 TH202 TH401 TH402,Thermistor_NTC,10k B3950,Resistor_SMD:R_0603_1608Metric,,
14,TP101 TP102 TP103 TP161 TP201 TP202 TP301 TP302 TP303 TP304 TP401 TP402 TP541 TP542,TestPoint,TestPoint,TestPoint:TestPoint_Pad_D1.0mm,,
1,U101,AP33772S,AP33772S,Package_DFN_QFN:QFN-24-1EP_4x4mm_P0.5mm_EP2.7x2.7mm_ThermalVias,C50341643,
2,U102 U161,LM74800,LM74800,Package_SON:WSON-12-1EP_3x3mm_P0.5mm_EP1.5x2.5mm,C3215600,
2,U181 U401,INA228,INA228,Package_SO:TSSOP-10_3x3mm_P0.5mm,C2887910,
1,U201,LTC7803,LTC7803,Package_SO:MSOP-16-1EP_3x4.039mm_P0.5mm_EP1.651x2.845mm_ThermalVias,C1016554,
1,U202,INA240A3PW,INA240A3PW,Package_SO:TSSOP-8_4.4x3mm_P0.65mm,C544538,
1,U301,ADA4522-2,ADA4522-2,Package_SO:SOIC-8_3.9x4.9mm_P1.27mm,C403697,
3,U302 U402 U403,LMV331,LMV331,Package_TO_SOT_SMD:SOT-23-5,,
1,U404,UCC27511ADBV,UCC27511ADBV,Package_TO_SOT_SMD:SOT-23-6,,
1,U405,VOM1271,VOM1271,Package_SO:SO-4_4.4x3.6mm_P2.54mm,C146286,
1,U541,LM5164DDA,LM5164DDA,Package_SO:HSOP-8-1EP_3.9x4.9mm_P1.27mm_EP2.41x3.1mm_ThermalVias,C477928,
1,U542,LP2985-5.0,LP2985-5.0,Package_TO_SOT_SMD:SOT-23-5,C74511,
